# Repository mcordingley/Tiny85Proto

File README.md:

# Tiny85Proto

A powered project board for ATTiny85 chips with regulated 5v on J1, GND on J2, and GPIO pins 0-4 on J3 pins 1-5.
Just add seven to twelve volts and ground on J4.

Parts list:

C1
: 0.33uF
C2
: 0.1uF
R2
: 10K ohm
U1
: LM7805
U2
: AT Tiny85

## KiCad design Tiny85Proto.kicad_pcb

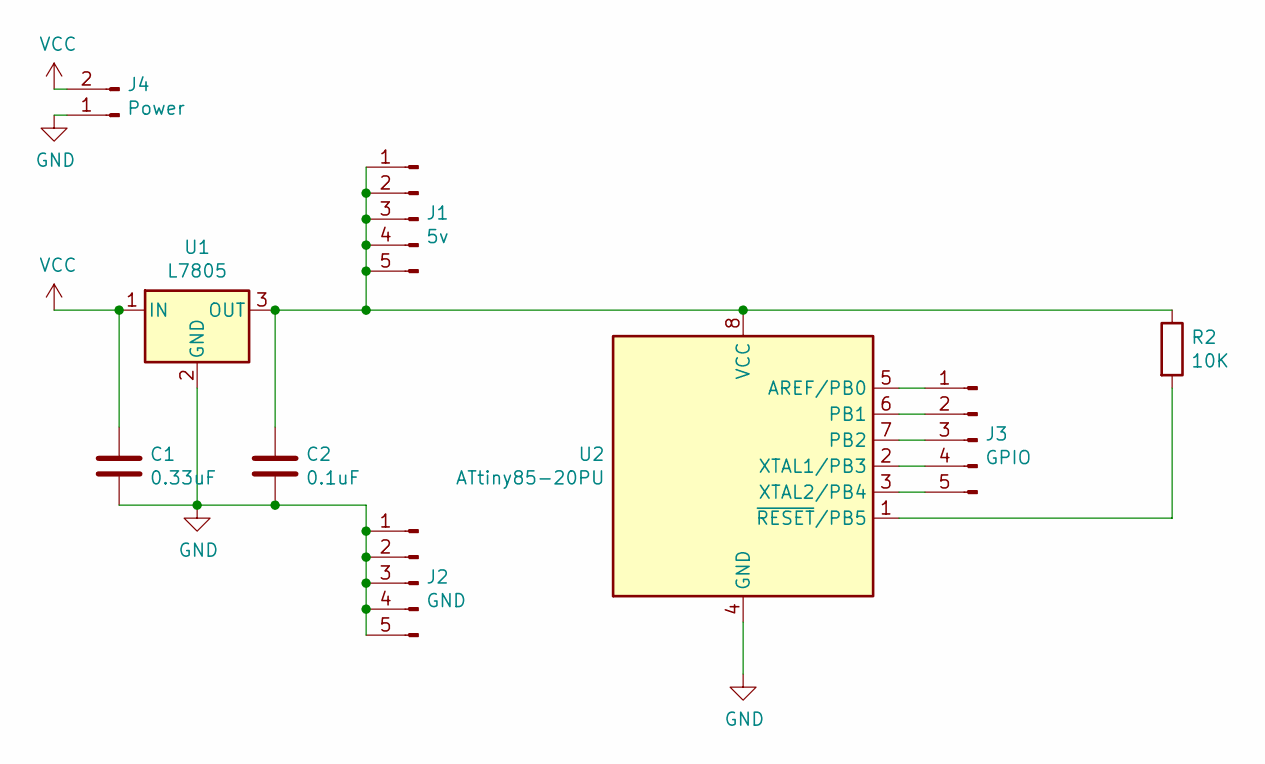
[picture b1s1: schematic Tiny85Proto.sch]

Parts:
C1: 0.33uF; C_Disc_D4.7mm_W2.5mm_P5.00mm
C2: 0.1uF; C_Disc_D4.7mm_W2.5mm_P5.00mm
J1: 5v; PinHeader_1x05_P2.54mm_Vertical
J2: GND; PinHeader_1x05_P2.54mm_Vertical
J3: GPIO; PinHeader_1x05_P2.54mm_Vertical
J4: Power; PinHeader_1x02_P2.54mm_Vertical
R2: 10K; R_Axial_DIN0207_L6.3mm_D2.5mm_P7.62mm_Horizontal
U1: L7805; TO-220-3_Vertical
U2: ATtiny85-20PU; DIP-8_W7.62mm

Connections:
GND: C1.2, C2.2, J2.1, J2.2, J2.3, J2.4, J2.5, J4.1, U1.2 (GND), U2.4 (GND)
unnamed: C2.1, J1.1, J1.2, J1.3, J1.4, J1.5, R2.1, U1.3 (OUT), U2.8 (VCC)
unnamed: J3.1, U2.5 (AREF/PB0)
unnamed: J3.2, U2.6 (PB1)
unnamed: J3.3, U2.7 (PB2)
unnamed: J3.4, U2.2 (XTAL1/PB3)
unnamed: J3.5, U2.3 (XTAL2/PB4)
unnamed: R2.2, U2.1 (~RESET~/PB5)
VCC: C1.1, J4.2, U1.1 (IN)

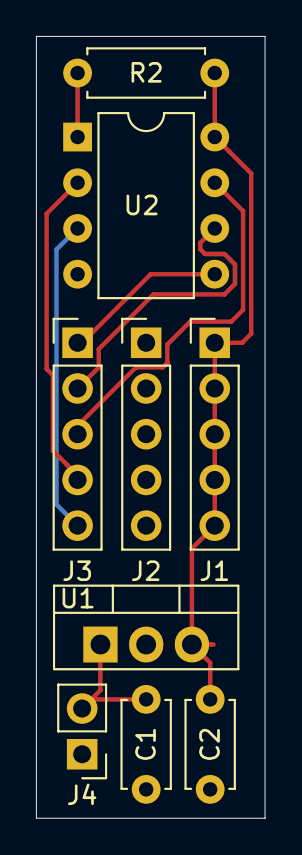
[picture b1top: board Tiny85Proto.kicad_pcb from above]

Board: 2 copper layers, 12.7 x 43.4 mm, 9 parts (0 on the bottom side), 9 nets.

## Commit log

2020-06-13 Import project.
2020-06-16 Add documentation.
2020-06-16 Remove cache files.
2020-06-16 Ignore cache files.
2020-06-16 MIT license.
